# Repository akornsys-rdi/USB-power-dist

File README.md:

# USB-power-dist

Simple USB power distribution with dual DCP

# USB power dist

    2x USB DCP identified w/ current limit
    RATINGS:
        MAX CURRENT -> 12.8434A (track width)
        MAX CURRENT -> 16A (screw conn)
        MAX CURRENT -> 3A/PORT (USB conn)

# Crossover

    Invert VCC & GND lines, high current capability

# Power good monitor

    Switch off if voltage > 5.25 < 4.45, led & pin output + FUSE

# Power supply

    6 to 26V input to 5.2V @ 6.5A (LM25085)

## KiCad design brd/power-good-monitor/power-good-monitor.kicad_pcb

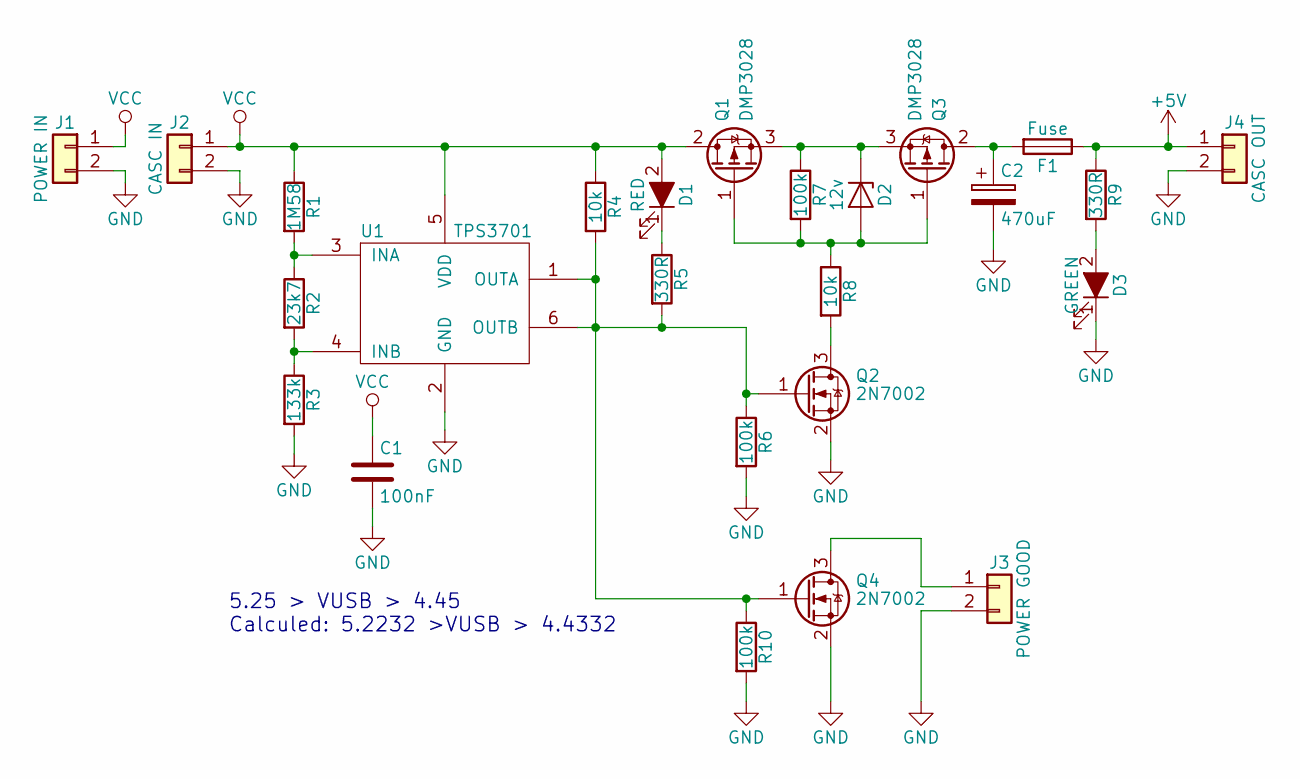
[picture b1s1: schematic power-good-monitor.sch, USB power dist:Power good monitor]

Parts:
C1: 100nF; C_0805_HandSoldering
C2: 470uF; CP_Elec_8x10
D1: RED; LED_0805_HandSoldering
D2: 12v; D_SOD-123
D3: GREEN; LED_0805_HandSoldering
F1: Fuse; Fuse_0679H
J1: POWER IN; TerminalBlock_Pheonix_MKDS1.5-2pol
J2: CASC IN; WireConnection_2.50mmDrill_LargePad
J3: POWER GOOD; Molex_KK-6410-02_02x2.54mm_Straight
J4: CASC OUT; WireConnection_2.50mmDrill_LargePad
Q1, Q3: DMP3028; TO-252-2
Q2, Q4: 2N7002; SOT-23_Handsoldering
R1: 1M58; R_0805_HandSoldering
R2: 23k7; R_0805_HandSoldering
R3: 133k; R_0805_HandSoldering
R4, R8: 10k; R_0805_HandSoldering
R5, R9: 330R; R_0805_HandSoldering
R6, R7, R10: 100k; R_0805_HandSoldering
U1: TPS3701; SOT-23-6_Handsoldering

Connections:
+5V: F1.1, J4.1, R9.1
GND: C1.2, C2.2, D3.1 (K), J1.2, J2.2, J3.2, J4.2, Q2.2 (S), Q4.2 (S), R3.2, R6.2, R10.2, U1.2 (GND)
unnamed: C2.1, F1.2, Q3.2 (D)
unnamed: D1.1 (K), R5.1
unnamed: D2.1 (K), Q1.3 (S), Q3.3 (S), R7.1
unnamed: D2.2 (A), Q1.1 (G), Q3.1 (G), R7.2, R8.1
unnamed: D3.2 (A), R9.2
unnamed: J3.1, Q4.3 (D)
unnamed: Q2.1 (G), Q4.1 (G), R4.2, R5.2, R6.1, R10.1, U1.1 (OUTA), U1.6 (OUTB)
unnamed: Q2.3 (D), R8.2
unnamed: R1.2, R2.1, U1.3 (INA)
unnamed: R2.2, R3.1, U1.4 (INB)
VCC: C1.1, D1.2 (A), J1.1, J2.1, Q1.2 (D), R1.1, R4.1, U1.5 (VDD)

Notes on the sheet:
5.25 > VUSB > 4.45 Calculed: 5.2232 >VUSB > 4.4332

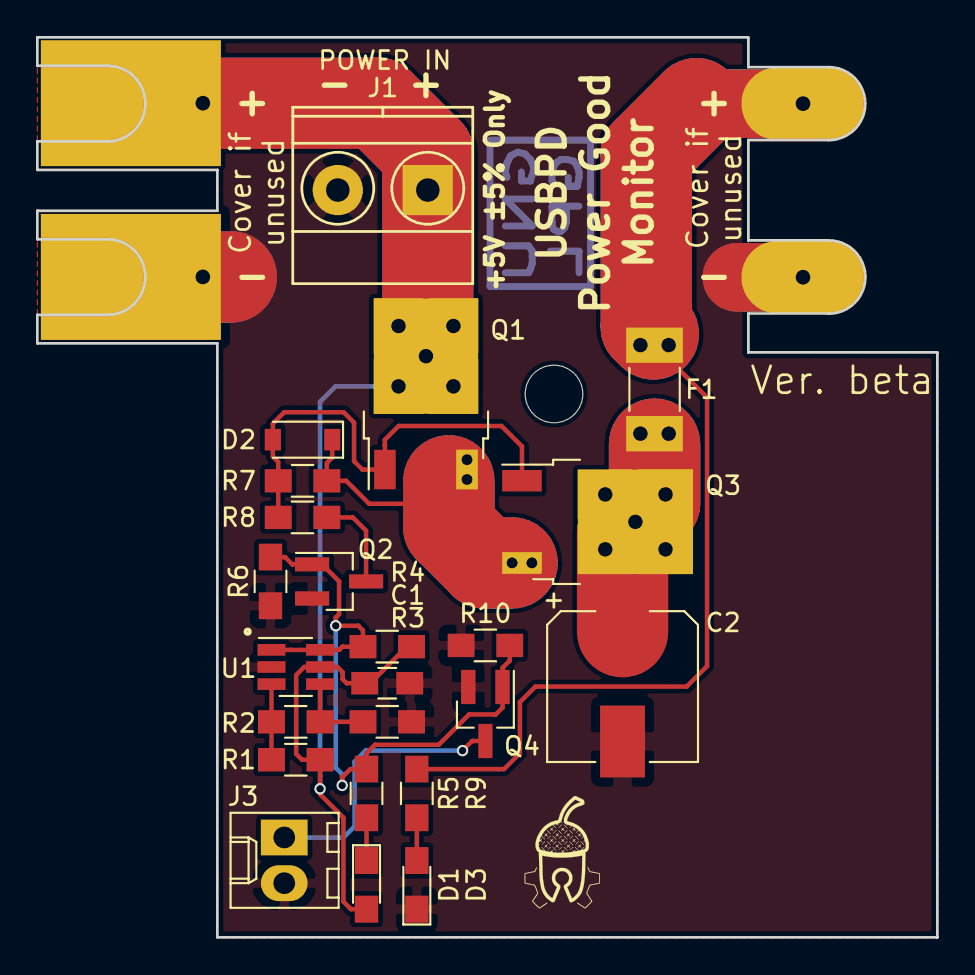
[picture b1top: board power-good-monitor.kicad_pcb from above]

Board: 2 copper layers, 50.0 x 50.0 mm, 25 parts (0 on the bottom side), 13 nets.

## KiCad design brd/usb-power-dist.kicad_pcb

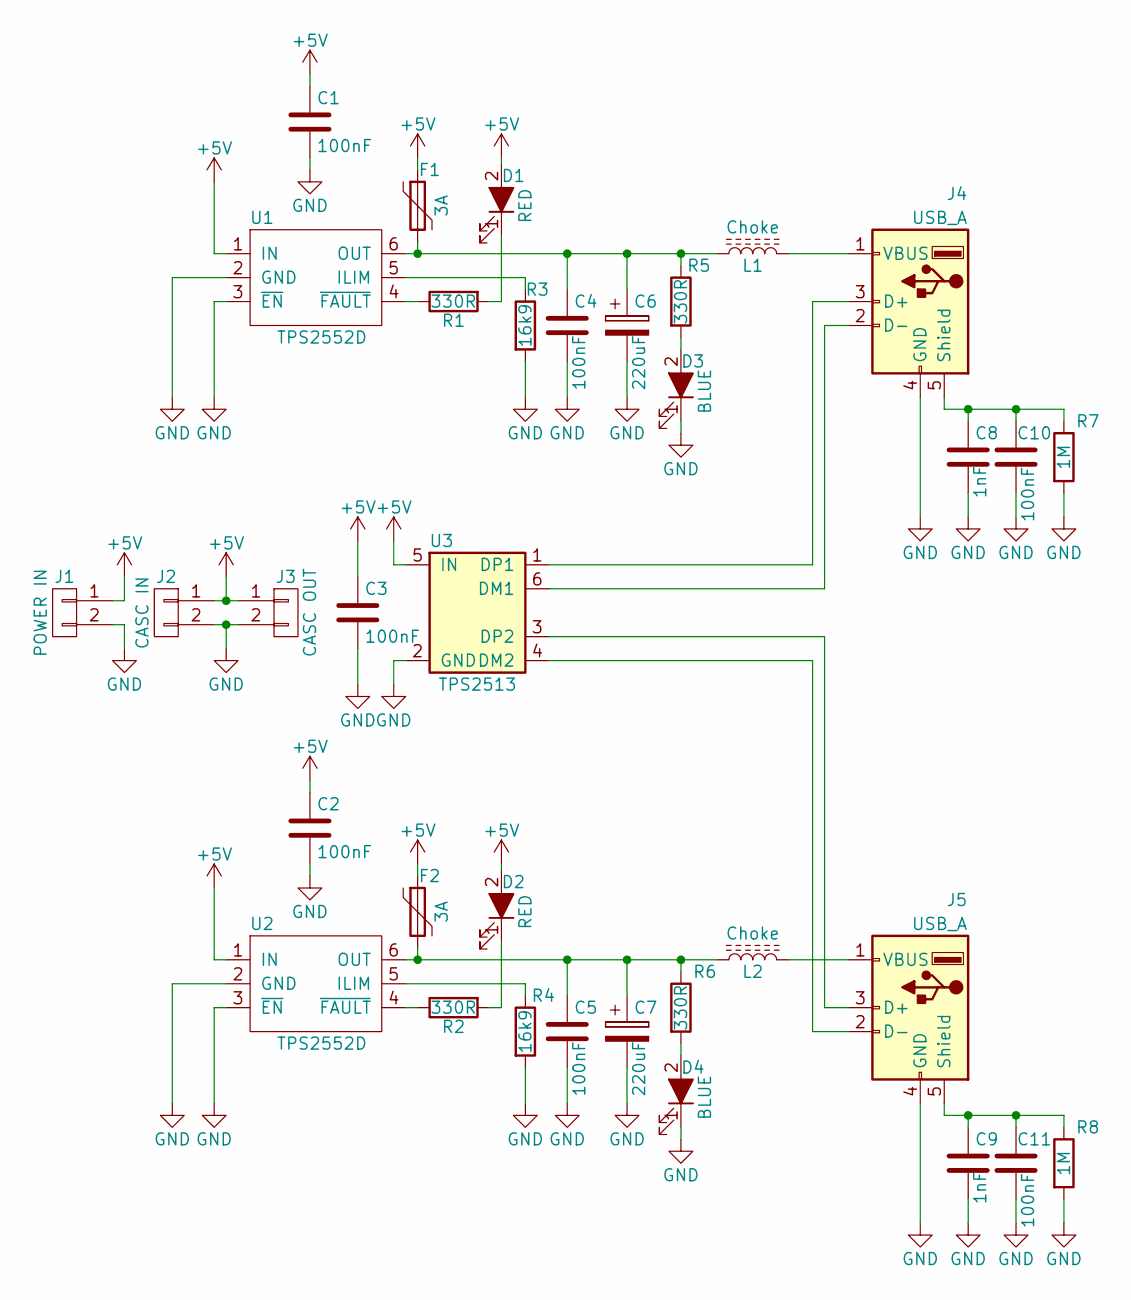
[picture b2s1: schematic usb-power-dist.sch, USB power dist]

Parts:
C1, C2, C3, C4, C5, C10, C11: 100nF; C_0805_HandSoldering
C6, C7: 220uF; CP_Elec_6.3x7.7
C8, C9: 1nF; C_0805_HandSoldering
D1, D2: RED; LED_0805
D3, D4: BLUE; LED_0805
F1, F2: 3A; Fuse_SMD1206_Wave
J1: POWER IN; TerminalBlock_Pheonix_MKDS1.5-2pol
J2: CASC IN; WireConnection_2.50mmDrill_LargePad
J3: CASC OUT; WireConnection_2.50mmDrill_LargePad
J4, J5: USB_A
L1, L2: Choke; L_0805_HandSoldering
R1, R2, R5, R6: 330R; R_0805_HandSoldering
R3, R4: 16k9; R_0805_HandSoldering
R7, R8: 1M; R_0805_HandSoldering
U1, U2: TPS2552D; SOT-23-6_Handsoldering
U3: TPS2513; SOT-23-6_Handsoldering

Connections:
+5V: C1.1, C2.1, C3.1, D1.2 (A), D2.2 (A), F1.1, F2.1, J1.1, J2.1, J3.1, U1.1 (IN), U2.1 (IN), U3.5 (IN)
/D1+: J4.3 (D+), U3.1 (DP1)
/D1-: J4.2 (D-), U3.6 (DM1)
/D2+: J5.3 (D+), U3.3 (DP2)
/D2-: J5.2 (D-), U3.4 (DM2)
GND: C1.2, C2.2, C3.2, C4.2, C5.2, C6.2, C7.2, C8.2, C9.2, C10.2, C11.2, D3.1 (K), D4.1 (K), J1.2, J2.2, J3.2, J4.4 (GND), J5.4 (GND), R3.2, R4.2, R7.2, R8.2, U1.2 (GND), U1.3 (~EN), U2.2 (GND), U2.3 (~EN), U3.2 (GND)
unnamed: C4.1, C6.1, F1.2, L1.1, R5.1, U1.6 (OUT)
unnamed: C5.1, C7.1, F2.2, L2.1, R6.1, U2.6 (OUT)
unnamed: C8.1, C10.1, J4.5 (Shield), R7.1
unnamed: C9.1, C11.1, J5.5 (Shield), R8.1
unnamed: D1.1 (K), R1.2
unnamed: D2.1 (K), R2.2
unnamed: D3.2 (A), R5.2
unnamed: D4.2 (A), R6.2
unnamed: J4.1 (VBUS), L1.2
unnamed: J5.1 (VBUS), L2.2
unnamed: R1.1, U1.4 (~FAULT)
unnamed: R2.1, U2.4 (~FAULT)
unnamed: R3.1, U1.5 (ILIM)
unnamed: R4.1, U2.5 (ILIM)

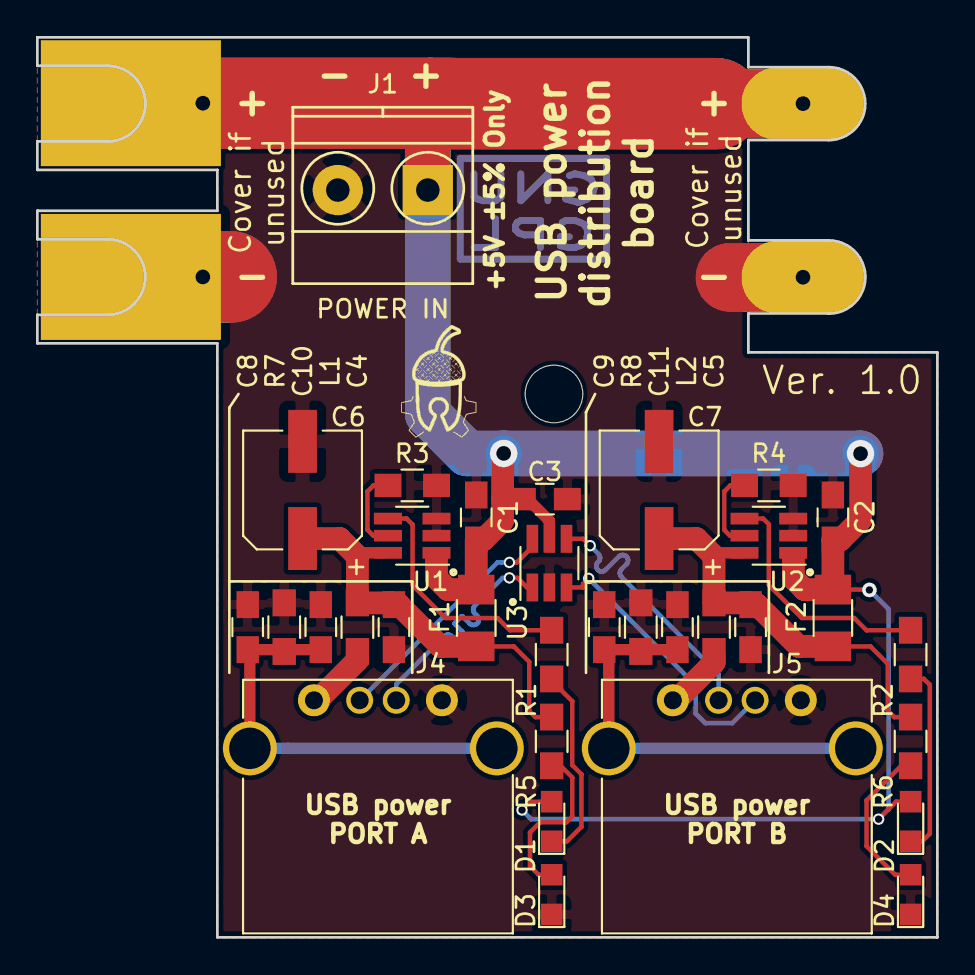
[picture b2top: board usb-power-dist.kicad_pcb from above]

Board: 2 copper layers, 50.0 x 50.0 mm, 35 parts (0 on the bottom side), 20 nets.

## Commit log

2017-04-12 comenzado a desarrollar pcb -wip
2017-04-20 resuelto contorno PCB, verificadas dimensiones, comprobado trazado y colocados componentes restantes -wip
2017-04-27 comprobada PCB
2017-04-27 generados gerbers
2017-04-28 eliminado cobre exterior a la placa
2017-04-28 añadidos datos en recuadro esquematico
2017-05-27 corregida asociacion de pines en integrado TPS2552
2017-05-27 corregido esquematico por error en asignacion de pines en TPS2552, modificado valor de condensador de salida
2017-05-27 corregido fallo por asignacion de pines, cambiado footprint de conector de bornes y condensadores de salida
2017-05-27 recolocados componentes por fallo en asignacion de pines en TPS2552, modificada posicion de serigrafias, añadida serigrafia de version y tabla de corriente, cambiado footprint de conector de entrada 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
2017-05-27 regenerados gerbers
2017-09-01 corregido fallo ausencia de pista pin ¬FAULT
2017-09-01 añadido plateado de contactos mediante vias, añadido marcado de PCB y verificacion general
2017-09-01 aumentado grosor union thermal en pads de GND
2017-09-01 regenerados gerbers version rc2
2017-09-04 descartado plateado de contactos mediante vias, reducidas tolerancias en su lugar
2017-09-04 regenerados gerbers rc3
2017-10-28 reconsideradas las opciones con respecto a ESD, EMI y shield grounding, añadidos chokes en alimentación y regenerada netlist
2017-10-28 modificado el esquemático para producción (eliminadas 0R, modificados valores de componentes), añadida protección para no limitación a través PPTC, añadido BoM, renumerado esquemático
2017-11-02 renombradas nets para pistas diferenciales, regenerada netlist
2017-11-02 recolocados componentes a una única cara y retrazadas pistas, a falta de serigrafía !wip
2017-11-02 añadido BoM
2017-11-02 editada serigrafía a falta de SN
2017-11-03 corregida colocacion de componentes invertidos y próximos, retocados trazados y tamaños de pad, editadas capas invisibles, establecido nuevo SN
2017-11-03 ordenadas librerias
2017-11-03 quitadas referencias conectores puzzle
2017-11-03 ordenado repo para nuevos módulos
2017-11-04 creada versión beta de placa `power good monitor`
2017-11-04 copiados logos akornsys a carpeta librerías
2017-11-05 restaurado README
2017-11-05 generado BoM
2017-11-05 creada versión beta de placa `power supply`
2017-11-05 regenerada netlist
2017-11-05 editado README
2017-11-05 creada versión beta de placa `crossover`
2017-11-06 añadida salida de drenador abierto a pin de estado
2017-11-06 añadidos nuevos componentes para salida de drenador abierto, editada serigrafia
2017-11-06 generados archivos gerbers
2017-11-06 subido archivo de referencia de especificaciones USB
2017-11-06 generada PCB
2017-11-06 generados archivos gerber
2017-11-06 diseñada PCB

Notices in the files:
brd/power-good-monitor/power-good-monitor.kicad_pcb:
Copyright © 201 kwendenarmo
Released under GNU/GPL 3 License https://www.gnu.org/licenses/gpl.html
Copyright © 2017 kwendenarmo
